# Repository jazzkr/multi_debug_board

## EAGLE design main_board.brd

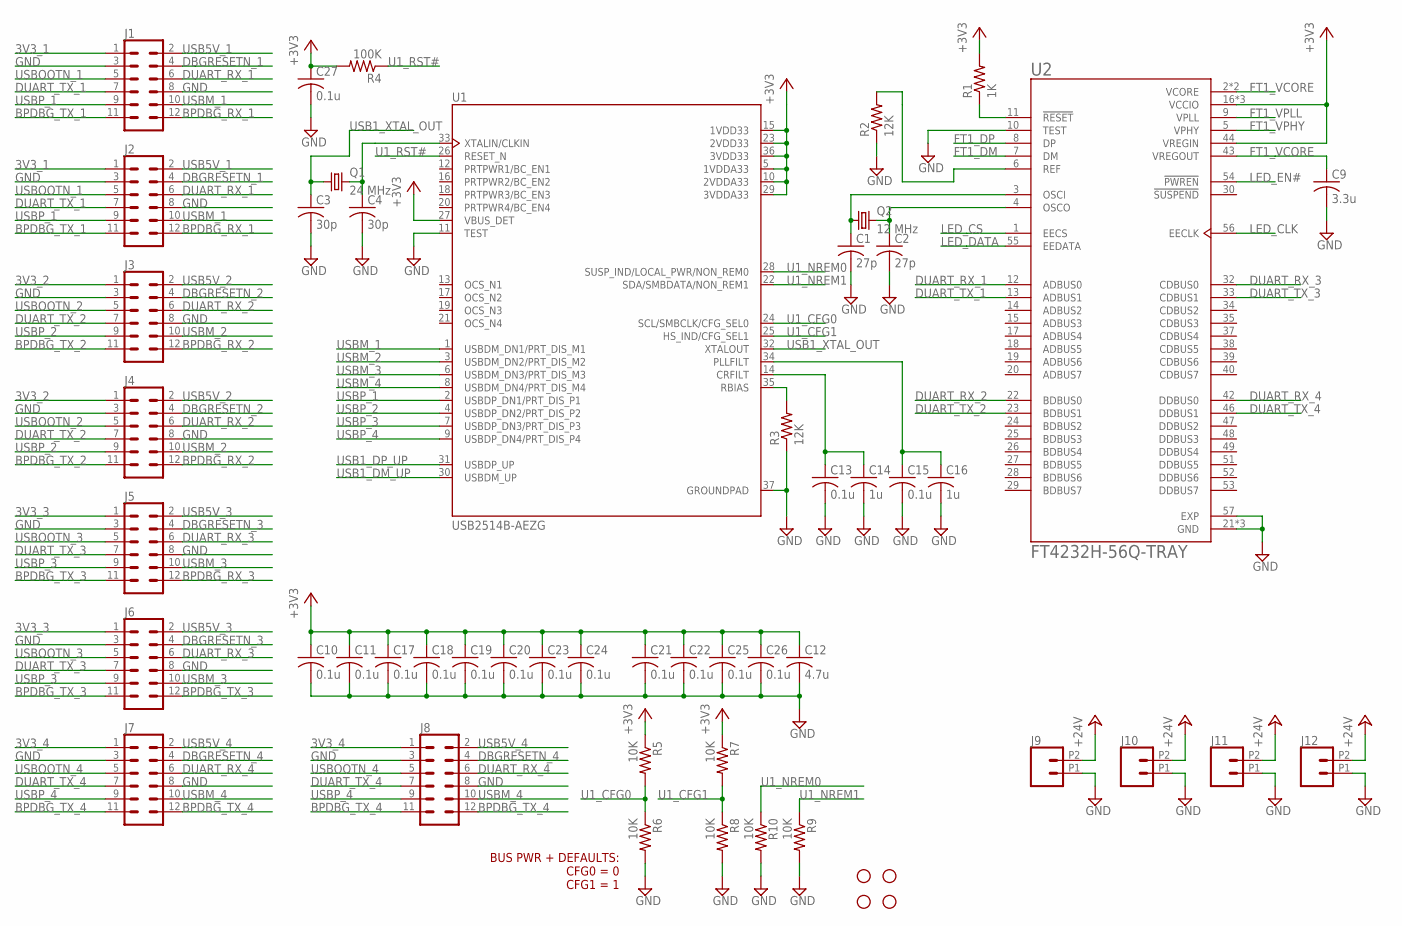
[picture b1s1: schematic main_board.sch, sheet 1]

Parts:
C1, C2: 27p; C0805K
C3, C4: 30p; C0805K
C9: 3.3u; C0805K
C10, C11, C13, C15, C17, C18, C19, C20, C21, C22, C23, C24, C25, C26, C27: 0.1u; C0805K
C12: 4.7u; C0805K
C14, C16: 1u; C0805K
H1, H2, H3, H4: STAND-OFF
J1, J2, J3, J4, J5, J6, J7, J8: CONN_06X2; 1X06_1.27MM
J9, J10, J11, J12: CONN_022.54MM_SCREWTERM; 1X02_2.54_SCREWTERM
Q1: 24 MHz; HC49UP
Q2: 12 MHz; HC49UP
R1: 1K; R0805
R2, R3: 12K; R0805
R4: 100K; R0805
R5, R6, R7, R8, R9, R10: 10K; R0805
U1: USB2514B-AEZG; VQFN50P600X600X100-36N
U2: FT4232H-56Q-TRAY; QFN50P800X800X100-57N

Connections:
3V3_1: J1.1, J2.1; also elsewhere on the board
3V3_2: J3.1, J4.1; also elsewhere on the board
3V3_3: J5.1, J6.1; also elsewhere on the board
3V3_4: J7.1, J8.1; also elsewhere on the board
+3V3: C10.1, C11.1, C12.1, C17.1, C18.1, C19.1, C20.1, C21.1, C22.1, C23.1, C24.1, C25.1, C26.1, C27.1, R1.2, R4.2, R5.1, R7.1, U1.5 (1VDDA33), U1.10 (2VDDA33), U1.15 (1VDD33), U1.23 (2VDD33), U1.27 (VBUS_DET), U1.29 (3VDDA33), U1.36 (3VDD33), U2.16 (VCCIO), U2.36 (VCCIO), U2.44 (VREGIN), U2.50 (VCCIO); also elsewhere on the board
+24V: J9.P2 (2), J10.P2 (2), J11.P2 (2), J12.P2 (2); also elsewhere on the board
BPDBG_RX_1: J1.12, J2.12; also elsewhere on the board
BPDBG_RX_2: J3.12, J4.12; also elsewhere on the board
BPDBG_RX_3: J5.12; also elsewhere on the board
BPDBG_TX_1: J1.11, J2.11; also elsewhere on the board
BPDBG_TX_2: J3.11, J4.11; also elsewhere on the board
BPDBG_TX_3: J5.11, J6.11, J6.12; also elsewhere on the board
BPDBG_TX_4: J7.11, J7.12, J8.11, J8.12; also elsewhere on the board
DBGRESETN_1: J1.4, J2.4; also elsewhere on the board
DBGRESETN_2: J3.4, J4.4; also elsewhere on the board
DBGRESETN_3: J5.4, J6.4; also elsewhere on the board
DBGRESETN_4: J7.4, J8.4; also elsewhere on the board
DUART_RX_1: J1.6, J2.6, U2.12 (ADBUS0); also elsewhere on the board
DUART_RX_2: J3.6, J4.6, U2.22 (BDBUS0); also elsewhere on the board
DUART_RX_3: J5.6, J6.6, U2.32 (CDBUS0); also elsewhere on the board
DUART_RX_4: J7.6, J8.6, U2.42 (DDBUS0); also elsewhere on the board
DUART_TX_1: J1.7, J2.7, U2.13 (ADBUS1); also elsewhere on the board
DUART_TX_2: J3.7, J4.7, U2.23 (BDBUS1); also elsewhere on the board
DUART_TX_3: J5.7, J6.7, U2.33 (CDBUS1); also elsewhere on the board
DUART_TX_4: J7.7, J8.7, U2.46 (DDBUS1); also elsewhere on the board
FT1_DM: U2.7 (DM)
FT1_DP: U2.8 (DP)
FT1_VCORE: C9.1, U2.2 (VCORE), U2.31 (VCORE), U2.43 (VREGOUT)
FT1_VPHY: U2.5 (VPHY)
FT1_VPLL: U2.9 (VPLL)
GND: C1.2, C2.2, C3.2, C4.2, C9.2, C10.2, C11.2, C12.2, C13.2, C14.2, C15.2, C16.2, C17.2, C18.2, C19.2, C20.2, C21.2, C22.2, C23.2, C24.2, C25.2, C26.2, C27.2, J1.3, J1.8, J2.3, J2.8, J3.3, J3.8, J4.3, J4.8, J5.3, J5.8, J6.3, J6.8, J7.3, J7.8, J8.3, J8.8, J9.P1 (1), J10.P1 (1), J11.P1 (1), J12.P1 (1), R2.1, R3.1, R6.2, R8.2, R9.2, R10.2, U1.11 (TEST), U1.37 (GROUNDPAD), U2.10 (TEST), U2.21 (GND), U2.41 (GND), U2.45 (GND), U2.57 (EXP); also elsewhere on the board
LED_CLK: U2.56 (EECLK)
LED_CS: U2.1 (EECS)
LED_DATA: U2.55 (EEDATA)
LED_EN#: U2.54 (!PWREN)
unnamed: C2.1, Q2.2, U2.4 (OSCO)
unnamed: C4.1, Q1.2, U1.33 (XTALIN/CLKIN)
unnamed: R3.2, U1.35 (RBIAS)
unnamed: C1.1, Q2.1, U2.3 (OSCI)
unnamed: C15.1, C16.1, U1.34 (PLLFILT)
unnamed: C13.1, C14.1, U1.14 (CRFILT)
unnamed: R2.2, U2.6 (REF)
unnamed: R1.1, U2.11 (!RESET)
U1_CFG0: R5.2, R6.1, U1.24 (SCL/SMBCLK/CFG_SEL0)
U1_CFG1: R7.2, R8.1, U1.25 (HS_IND/CFG_SEL1)
U1_NREM0: R10.1, U1.28 (SUSP_IND/LOCAL_PWR/NON_REM0)
U1_NREM1: R9.1, U1.22 (SDA/SMBDATA/NON_REM1)
U1_RST#: R4.1, U1.26 (RESET_N)
USB1_DM_UP: U1.30 (USBDM_UP)
USB1_DP_UP: U1.31 (USBDP_UP)
USB1_XTAL_OUT: C3.1, Q1.1, U1.32 (XTALOUT)
USB5V_1: J1.2, J2.2; also elsewhere on the board
USB5V_2: J3.2, J4.2; also elsewhere on the board
USB5V_3: J5.2, J6.2; also elsewhere on the board
USB5V_4: J7.2, J8.2; also elsewhere on the board
USBM_1: J1.10, J2.10, U1.1 (USBDM_DN1/PRT_DIS_M1); also elsewhere on the board
USBM_2: J3.10, J4.10, U1.3 (USBDM_DN2/PRT_DIS_M2); also elsewhere on the board
USBM_3: J5.10, J6.10, U1.6 (USBDM_DN3/PRT_DIS_M3); also elsewhere on the board
USBM_4: J7.10, J8.10, U1.8 (USBDM_DN4/PRT_DIS_M4); also elsewhere on the board
USBOOTN_1: J1.5, J2.5; also elsewhere on the board
USBOOTN_2: J3.5, J4.5; also elsewhere on the board
USBOOTN_3: J5.5, J6.5; also elsewhere on the board
USBOOTN_4: J7.5, J8.5; also elsewhere on the board
USBP_1: J1.9, J2.9, U1.2 (USBDP_DN1/PRT_DIS_P1); also elsewhere on the board
USBP_2: J3.9, J4.9, U1.4 (USBDP_DN2/PRT_DIS_P2); also elsewhere on the board
USBP_3: J5.9, J6.9, U1.7 (USBDP_DN3/PRT_DIS_P3); also elsewhere on the board
USBP_4: J7.9, J8.9, U1.9 (USBDP_DN4/PRT_DIS_P4); also elsewhere on the board

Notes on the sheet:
BUS PWR + DEFAULTS: CFG0 = 0 CFG1 = 1

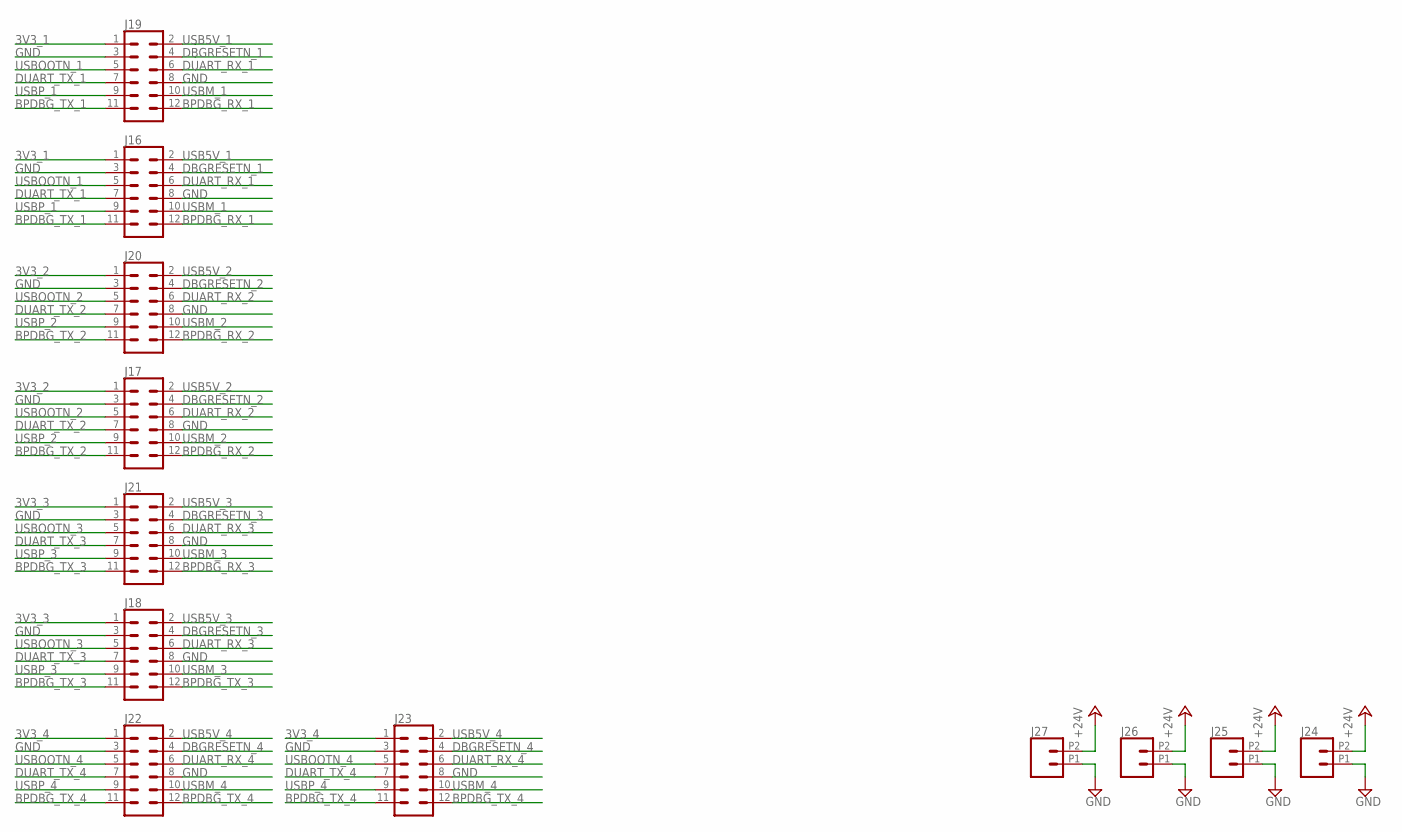
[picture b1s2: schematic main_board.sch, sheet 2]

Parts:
J16, J17, J18, J19, J20, J21, J22, J23: CONN_06X2; 1X06_1.27MM
J24, J25, J26, J27: CONN_022.54MM_SCREWTERM; 1X02_2.54_SCREWTERM

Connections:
3V3_1: J16.1, J19.1; also elsewhere on the board
3V3_2: J17.1, J20.1; also elsewhere on the board
3V3_3: J18.1, J21.1; also elsewhere on the board
3V3_4: J22.1, J23.1; also elsewhere on the board
+24V: J24.P2 (2), J25.P2 (2), J26.P2 (2), J27.P2 (2); also elsewhere on the board
BPDBG_RX_1: J16.12, J19.12; also elsewhere on the board
BPDBG_RX_2: J17.12, J20.12; also elsewhere on the board
BPDBG_RX_3: J21.12; also elsewhere on the board
BPDBG_TX_1: J16.11, J19.11; also elsewhere on the board
BPDBG_TX_2: J17.11, J20.11; also elsewhere on the board
BPDBG_TX_3: J18.11, J18.12, J21.11; also elsewhere on the board
BPDBG_TX_4: J22.11, J22.12, J23.11, J23.12; also elsewhere on the board
DBGRESETN_1: J16.4, J19.4; also elsewhere on the board
DBGRESETN_2: J17.4, J20.4; also elsewhere on the board
DBGRESETN_3: J18.4, J21.4; also elsewhere on the board
DBGRESETN_4: J22.4, J23.4; also elsewhere on the board
DUART_RX_1: J16.6, J19.6; also elsewhere on the board
DUART_RX_2: J17.6, J20.6; also elsewhere on the board
DUART_RX_3: J18.6, J21.6; also elsewhere on the board
DUART_RX_4: J22.6, J23.6; also elsewhere on the board
DUART_TX_1: J16.7, J19.7; also elsewhere on the board
DUART_TX_2: J17.7, J20.7; also elsewhere on the board
DUART_TX_3: J18.7, J21.7; also elsewhere on the board
DUART_TX_4: J22.7, J23.7; also elsewhere on the board
GND: J16.3, J16.8, J17.3, J17.8, J18.3, J18.8, J19.3, J19.8, J20.3, J20.8, J21.3, J21.8, J22.3, J22.8, J23.3, J23.8, J24.P1 (1), J25.P1 (1), J26.P1 (1), J27.P1 (1); also elsewhere on the board
USB5V_1: J16.2, J19.2; also elsewhere on the board
USB5V_2: J17.2, J20.2; also elsewhere on the board
USB5V_3: J18.2, J21.2; also elsewhere on the board
USB5V_4: J22.2, J23.2; also elsewhere on the board
USBM_1: J16.10, J19.10; also elsewhere on the board
USBM_2: J17.10, J20.10; also elsewhere on the board
USBM_3: J18.10, J21.10; also elsewhere on the board
USBM_4: J22.10, J23.10; also elsewhere on the board
USBOOTN_1: J16.5, J19.5; also elsewhere on the board
USBOOTN_2: J17.5, J20.5; also elsewhere on the board
USBOOTN_3: J18.5, J21.5; also elsewhere on the board
USBOOTN_4: J22.5, J23.5; also elsewhere on the board
USBP_1: J16.9, J19.9; also elsewhere on the board
USBP_2: J17.9, J20.9; also elsewhere on the board
USBP_3: J18.9, J21.9; also elsewhere on the board
USBP_4: J22.9, J23.9; also elsewhere on the board

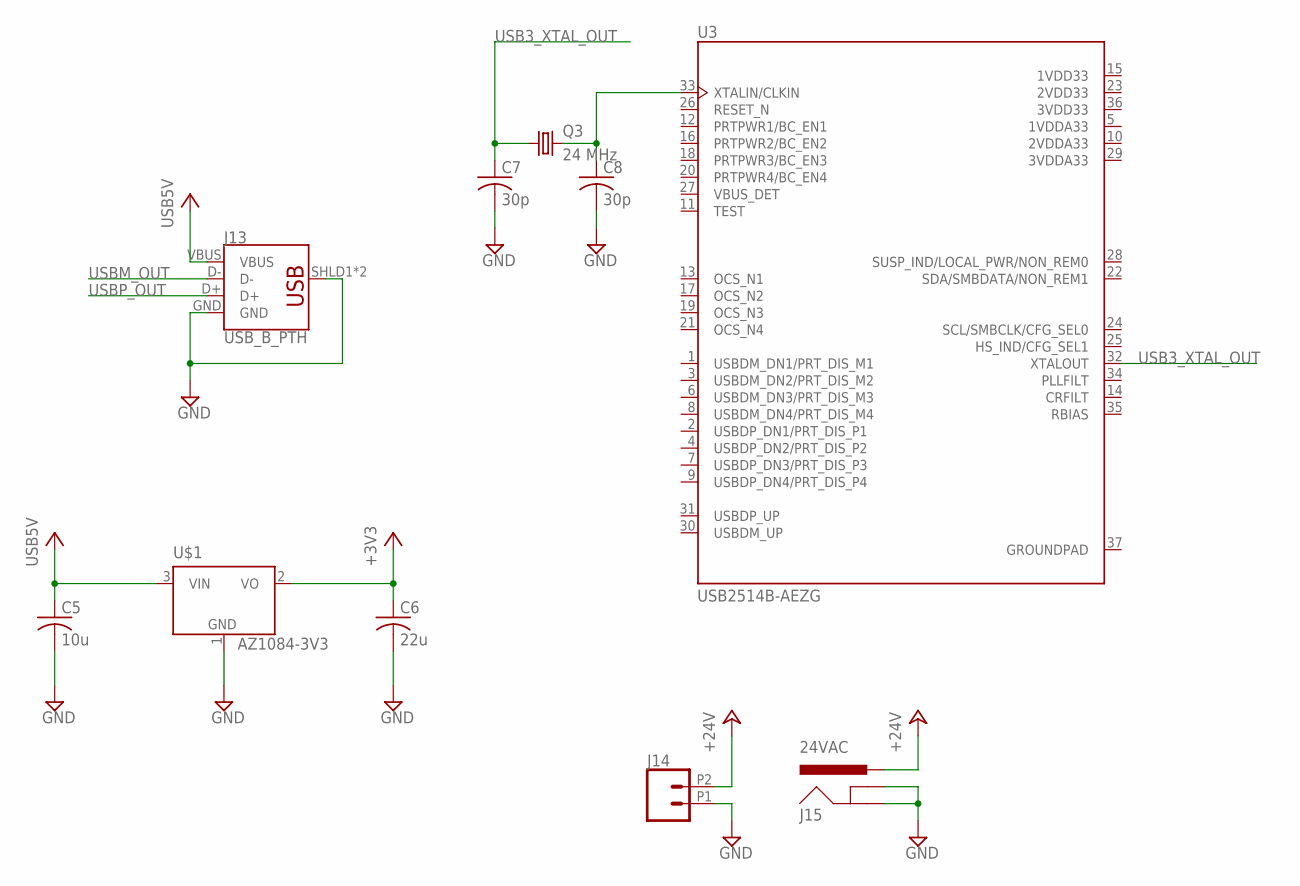
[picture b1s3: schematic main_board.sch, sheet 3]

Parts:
C5: 10u; C0805K
C6: 22u; C0805K
C7, C8: 30p; C0805K
J13: USB_B_PTH; USB-B-PTH
J14: CONN_022.54MM_SCREWTERM; 1X02_2.54_SCREWTERM
J15: 24VAC; POWER_JACK_SMD
Q3: 24 MHz; HC49UP
U3: USB2514B-AEZG; VQFN50P600X600X100-36N
U$1: AZ1084-3V3; TO254P1435X457-4N

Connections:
1VDD33: U3.15 (1VDD33)
1VDDA33: U3.5 (1VDDA33)
2VDD33: U3.23 (2VDD33)
2VDDA33: U3.10 (2VDDA33)
3VDD33: U3.36 (3VDD33)
+3V3: C6.1, U$1.2 (VO); also elsewhere on the board
+5V: C5.1, J13.VBUS, U$1.3 (VIN)
+24V: J14.P2 (2), J15.VIN0 (PWR); also elsewhere on the board
GND: C5.2, C6.2, C7.2, C8.2, J13.GND, J13.SHLD1 (SHIELD), J13.SHLD2 (SHIELD), J14.P1 (1), J15.GND (GNDBREAK), J15.P$4 (GND), U$1.1 (GND); also elsewhere on the board
GROUNDPAD: U3.37 (GROUNDPAD)
unnamed: C8.1, Q3.2, U3.33 (XTALIN/CLKIN)
USB3_XTAL_OUT: C7.1, Q3.1, U3.32 (XTALOUT)
USBM_OUT: J13.D-
USBP_OUT: J13.D+

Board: 2 copper layers, 75 parts (7 on the bottom side), 60 nets, no tracks yet.

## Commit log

2018-08-15 Committing progress

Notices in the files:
parts and their libraries:
connectors: Licensing: Creative Commons ShareAlike 4.0 International - https://creativecommons.org/licenses/by-sa/4.0
